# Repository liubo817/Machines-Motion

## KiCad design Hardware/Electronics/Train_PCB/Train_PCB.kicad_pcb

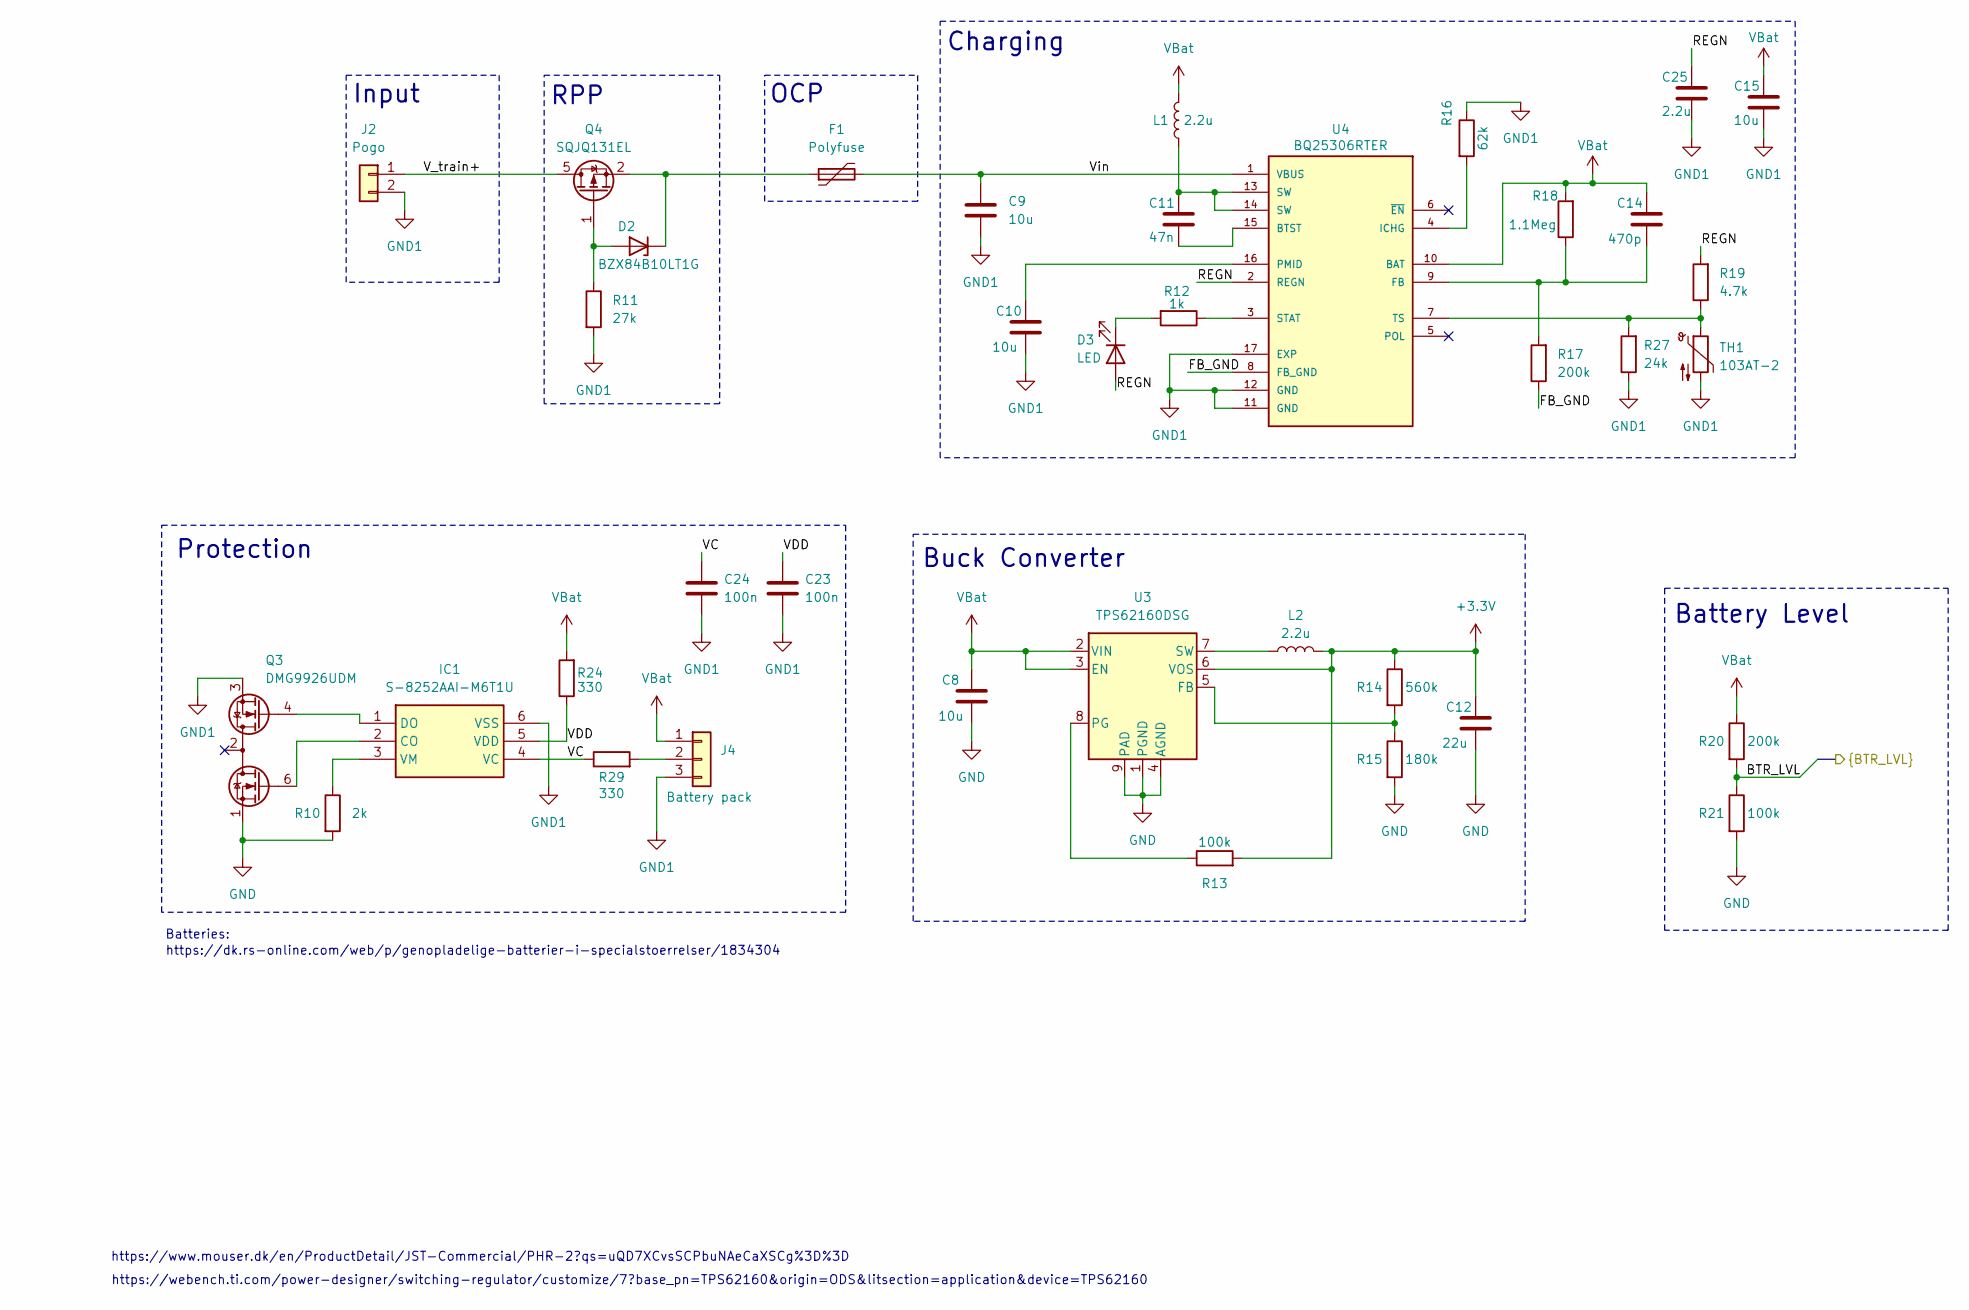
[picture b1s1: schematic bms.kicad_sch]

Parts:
C8, C9, C10, C15: 10u; C_0603_1608Metric
C11: 47n; C_0603_1608Metric
C12: 22u; C_0805_2012Metric
C14: 470p; C_0603_1608Metric
C23, C24: 100n; C_0603_1608Metric
C25: 2.2u; C_0603_1608Metric
D2: BZX84B10LT1G; SOT-23
D3: LED; 155060SS75300
F1: Polyfuse; 1812L010DR
IC1: S-8252AAI-M6T1U; SOT-23-6; Manufacturer_Part_Number S-8252ABU-M6T1U
J2: Pogo; JST_PH_S2B-PH-K_1x02_P2.00mm_Horizontal
J4: Battery pack; JST_PH_S3B-PH-K_1x03_P2.00mm_Horizontal
L1, L2: 2.2u; INDPM4042X200N
Q3: DMG9926UDM; SOT-23-6
Q4: SQJQ131EL; PowerPAK_SO-8_Single
R10: 2k; R_0603_1608Metric
R11: 27k; R_0603_1608Metric
R12: 1k; R_0603_1608Metric
R13, R21: 100k; R_0603_1608Metric
R14: 560k; R_0603_1608Metric
R15: 180k; R_0603_1608Metric
R16: 62k; R_0603_1608Metric
R17, R20: 200k; R_0603_1608Metric
R18: 1.1Meg; R_0603_1608Metric
R19: 4.7k; R_0603_1608Metric
R24, R29: 330; R_0603_1608Metric
R27: 24k; R_0603_1608Metric
TH1: 103AT-2; JST_PH_S2B-PH-K_1x02_P2.00mm_Horizontal
U3: TPS62160DSG; Texas_DSG0008A_WSON-8-1EP_2x2mm_P0.5mm_EP0.9x1.6mm_ThermalV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
U4: BQ25306RTER; WQFN-16-1EP_3x3mm_P0.5mm_EP1.68x1.68mm_ThermalVias; PARTREV A

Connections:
+3.3V: C12.1, L2.2, R13.2, R14.1, U3.6 (VOS); also elsewhere on the board
/BMS/BTR_LVL: R20.2, R21.1; also elsewhere on the board
/BMS/FB_GND: R17.1, U4.8 (FB_GND)
/BMS/REGN: C25.1, D3.2 (A), R19.2, U4.2 (REGN)
/BMS/VC: C24.1, IC1.4 (VC), R29.1
/BMS/VDD: C23.1, IC1.5 (VDD), R24.1
/BMS/V_train+: J2.1, Q4.5 (D)
/BMS/Vin: C9.1, F1.2, U4.1 (VBUS)
GND: C8.2, C12.2, Q3.1 (D1), R10.2, R15.2, R21.2, U3.1 (PGND), U3.4 (AGND), U3.9 (PAD); also elsewhere on the board
GND1: C9.2, C10.2, C15.2, C23.2, C24.2, C25.2, IC1.6 (VSS), J2.2, J4.3, Q3.3 (S2), R11.2, R16.1, R27.1, TH1.2, U4.11 (GND), U4.12 (GND), U4.17 (EXP)
unnamed: C11.1, L1.1, U4.13 (SW), U4.14 (SW)
unnamed: D2.1 (A), Q4.1 (G), R11.1
unnamed: D2.3 (K), F1.1, Q4.2 (S), Q4.3 (S), Q4.4 (S)
unnamed: D3.1 (K), R12.2
unnamed: IC1.2 (CO), Q3.6 (G1)
unnamed: IC1.1 (DO), Q3.4 (G2)
unnamed: IC1.3 (VM), R10.1
unnamed: J4.2, R29.2
unnamed: R14.2, R15.1, U3.5 (FB)
unnamed: R13.1, U3.8 (PG)
unnamed: L2.1, U3.7 (SW)
unnamed: C11.2, U4.15 (BTST)
unnamed: C14.2, R17.2, R18.1, U4.9 (FB)
unnamed: R16.2, U4.4 (ICHG)
unnamed: C10.1, U4.16 (PMID)
unnamed: R12.1, U4.3 (STAT)
unnamed: R19.1, R27.2, TH1.1, U4.7 (TS)
VBat: C8.1, C14.1, C15.1, J4.1, L1.2, R18.2, R20.1, R24.2, U3.2 (VIN), U3.3 (EN), U4.10 (BAT); also elsewhere on the board

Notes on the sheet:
https://www.mouser.dk/en/ProductDetail/JST-Commercial/PHR-2?qs=uQD7XCvsSCPbuNAeCaXSCg%3D%3D
https://dk.rs-online.com/web/p/genopladelige-batterier-i-specialstoerrelser/1834304
Batteries:
https://webench.ti.com/power-designer/switching-regulator/customize/7?base_pn=TPS62160&origin=ODS&litsection=application&device=TPS62160
Protection
Buck Converter
OCP
Input
RPP
Charging
Battery Level

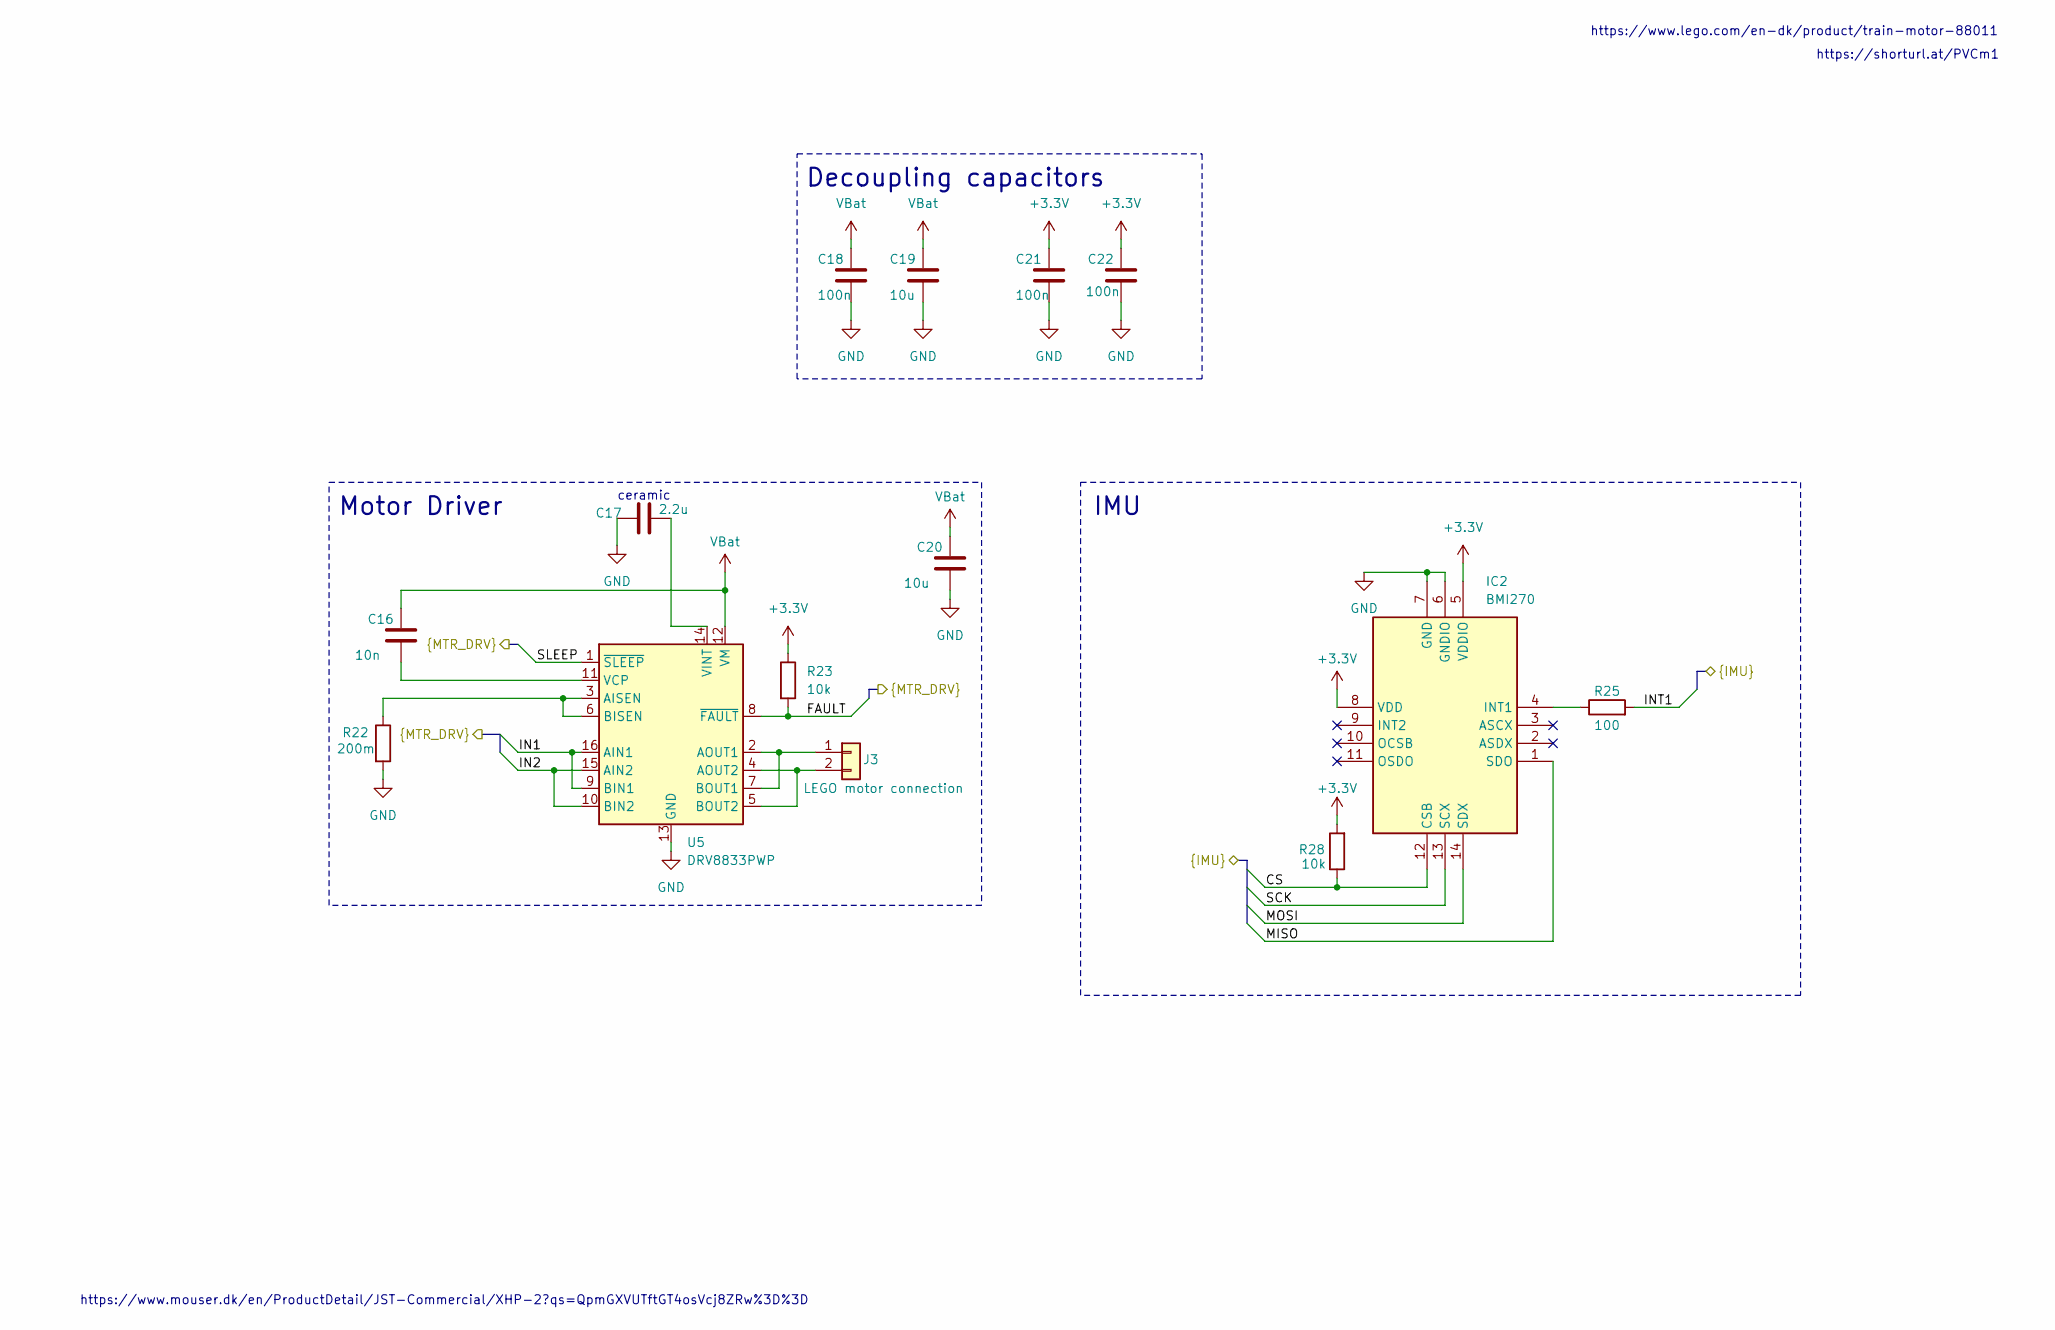
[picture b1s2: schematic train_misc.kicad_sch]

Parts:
C16: 10n; C_0603_1608Metric
C17: 2.2u; C_0603_1608Metric
C18, C21, C22: 100n; C_0603_1608Metric
C19: 10u; C_0603_1608Metric
C20: 10u; C_0805_2012Metric
IC2: BMI270; Mouser Part Number 262-BMI270
J3: LEGO motor connection; JST_XH_S2B-XH-A-1_1x02_P2.50mm_Horizontal
R22: 200m; R_0603_1608Metric
R23, R28: 10k; R_0603_1608Metric
R25: 100; R_0603_1608Metric
U5: DRV8833PWP; HTSSOP-16-1EP_4.4x5mm_P0.65mm_EP3.4x5mm_Mask2.66x2.46mm_The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

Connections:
+3.3V: C21.1, C22.1, IC2.5 (VDDIO), IC2.8 (VDD), R23.1, R28.2; also elsewhere on the board
/Esp32/CS: IC2.12 (CSB), R28.1; also elsewhere on the board
/Esp32/FAULT: R23.2, U5.8 (~FAULT); also elsewhere on the board
/Esp32/IN1: U5.9 (BIN1), U5.16 (AIN1); also elsewhere on the board
/Esp32/IN2: U5.10 (BIN2), U5.15 (AIN2); also elsewhere on the board
/Esp32/INT1: R25.2; also elsewhere on the board
/Esp32/MISO: IC2.1 (SDO); also elsewhere on the board
/Esp32/MOSI: IC2.14 (SDX); also elsewhere on the board
/Esp32/SCK: IC2.13 (SCX); also elsewhere on the board
/Esp32/SLEEP: U5.1 (~SLEEP); also elsewhere on the board
GND: C17.1, C18.2, C19.2, C20.2, C21.2, C22.2, IC2.6 (GNDIO), IC2.7 (GND), R22.2, U5.13 (GND), U5.17 (GND); also elsewhere on the board
unnamed: IC2.4 (INT1), R25.1
unnamed: J3.1, U5.2 (AOUT1), U5.7 (BOUT1)
unnamed: J3.2, U5.4 (AOUT2), U5.5 (BOUT2)
unnamed: R22.1, U5.3 (AISEN), U5.6 (BISEN)
unnamed: C16.2, U5.11 (VCP)
unnamed: C17.2, U5.14 (VINT)
VBat: C16.1, C18.1, C19.1, C20.1, U5.12 (VM); also elsewhere on the board

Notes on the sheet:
ceramic
Motor Driver
https://www.lego.com/en-dk/product/train-motor-88011
https://www.mouser.dk/en/ProductDetail/JST-Commercial/XHP-2?qs=QpmGXVUTftGT4osVcj8ZRw%3D%3D
https://shorturl.at/PVCm1
IMU
Decoupling capacitors

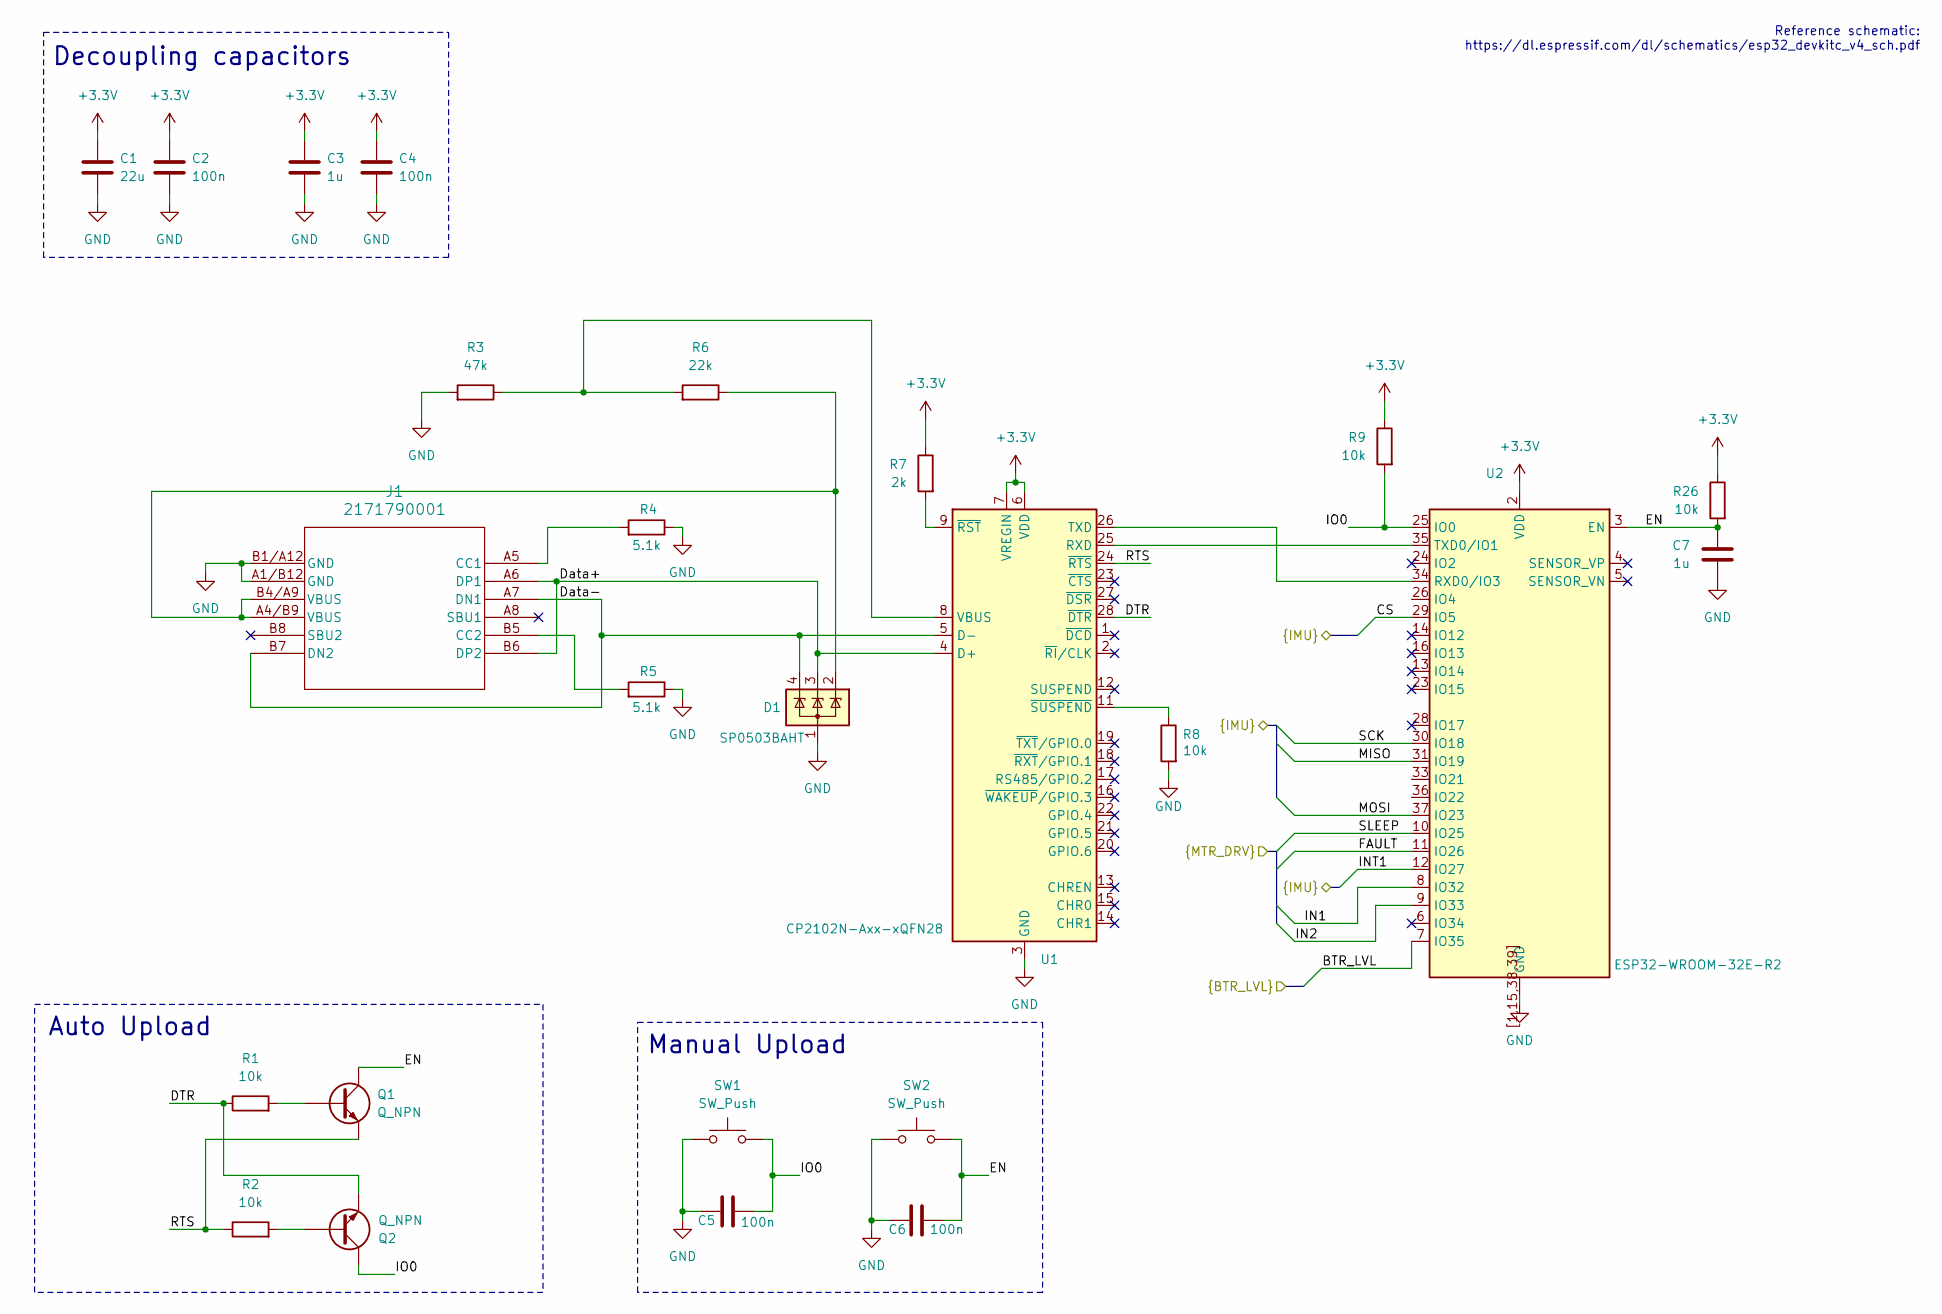
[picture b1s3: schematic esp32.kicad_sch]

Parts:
C1: 22u; C_0805_2012Metric
C2, C4, C5, C6: 100n; C_0603_1608Metric
C3, C7: 1u; C_0603_1608Metric
D1: SP0503BAHT; SP0503BAHTG
J1: 2171790001; 2171790001_MOL
Q1, Q2: Q_NPN; SOT-23-3
R1, R2, R8, R9, R26: 10k; R_0603_1608Metric
R3: 47k; R_0603_1608Metric
R4, R5: 5.1k; R_0603_1608Metric
R6: 22k; R_0603_1608Metric
R7: 2k; R_0603_1608Metric
SW1, SW2: SW_Push; EVPAWCD4A
U1: CP2102N-Axx-xQFN28; QFN-28-1EP_5x5mm_P0.5mm_EP3.1x3.1mm_ThermalVias
U2: ESP32-WROOM-32E-R2; ESP32-WROOM-32E

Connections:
+3.3V: C1.1, C2.1, C3.1, C4.1, R7.1, R9.1, R26.1, U1.6 (VDD), U1.7 (VREGIN), U2.2 (VDD); also elsewhere on the board
/BMS/BTR_LVL: U2.7 (IO35); also elsewhere on the board
/Esp32/CS: U2.29 (IO5); also elsewhere on the board
/Esp32/DTR: Q2.2 (E), R1.1, U1.28 (~DTR)
/Esp32/Data+: D1.3 (K), J1.A6 (DP1), J1.B6 (DP2), U1.4 (D+)
/Esp32/Data-: D1.4 (K), J1.A7 (DN1), J1.B7 (DN2), U1.5 (D-)
/Esp32/EN: C6.1, C7.1, Q1.3 (C), R26.2, SW2.2, U2.3 (EN)
/Esp32/FAULT: U2.11 (IO26); also elsewhere on the board
/Esp32/IN1: U2.8 (IO32); also elsewhere on the board
/Esp32/IN2: U2.9 (IO33); also elsewhere on the board
/Esp32/INT1: U2.12 (IO27); also elsewhere on the board
/Esp32/IO0: C5.1, Q2.3 (C), R9.2, SW1.2, U2.25 (IO0)
/Esp32/MISO: U2.31 (IO19); also elsewhere on the board
/Esp32/MOSI: U2.37 (IO23); also elsewhere on the board
/Esp32/RTS: Q1.2 (E), R2.1, U1.24 (~RTS)
/Esp32/SCK: U2.30 (IO18); also elsewhere on the board
/Esp32/SLEEP: U2.10 (IO25); also elsewhere on the board
GND: C1.2, C2.2, C3.2, C4.2, C5.2, C6.2, C7.2, D1.1 (A), J1.A1/B12 (GND), J1.B1/A12 (GND), R3.2, R4.1, R5.1, R8.2, SW1.1, SW2.1, U1.3 (GND), U1.29 (GND), U2.1 (GND), U2.15 (GND), U2.38 (GND), U2.39 (GND), U2.[1,15,38,39] (GND); also elsewhere on the board
unnamed: D1.2 (K), J1.A4/B9 (VBUS), J1.B4/A9 (VBUS), R6.1
unnamed: J1.A5 (CC1), R4.2
unnamed: J1.B5 (CC2), R5.2
unnamed: Q1.1 (B), R1.2
unnamed: Q2.1 (B), R2.2
unnamed: U1.25 (RXD), U2.35 (TXD0/IO1)
unnamed: U1.26 (TXD), U2.34 (RXD0/IO3)
unnamed: R3.1, R6.2, U1.8 (VBUS)
unnamed: R7.2, U1.9 (~RST)
unnamed: R8.1, U1.11 (~SUSPEND)

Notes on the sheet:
Reference schematic: https://dl.espressif.com/dl/schematics/esp32_devkitc_v4_sch.pdf
Decoupling capacitors
Manual Upload
Auto Upload

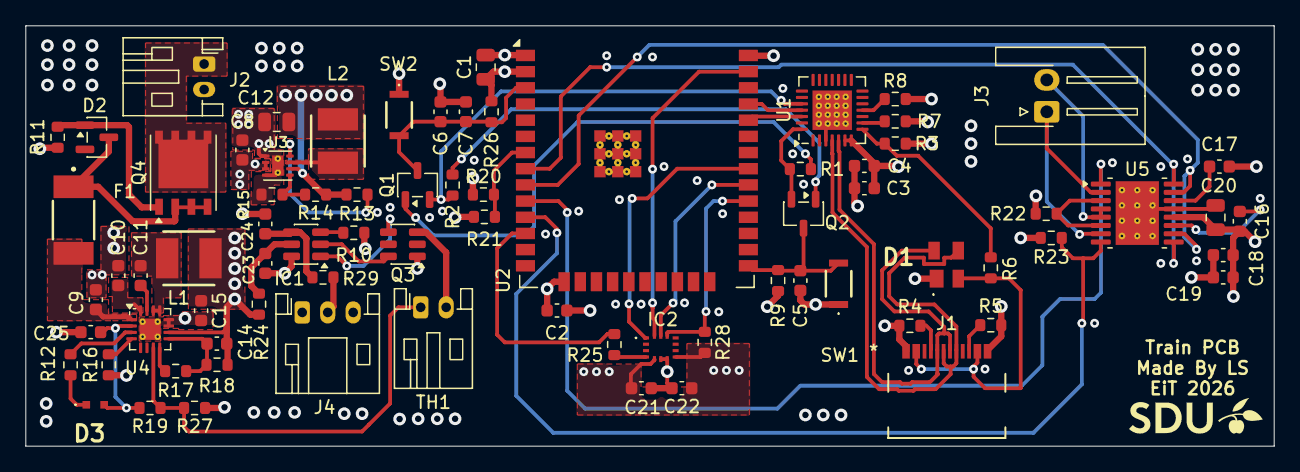
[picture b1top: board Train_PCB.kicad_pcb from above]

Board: 4 copper layers, 98.0 x 33.0 mm, 77 parts (0 on the bottom side), 59 nets.

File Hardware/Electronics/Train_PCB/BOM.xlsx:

Qty | Value | Parts | Device | Package | Description | Mouser | RS | Digikey
2 | 22uF | C1, C12 | C | C0805 | Capacitor
7 | 100nF | C2, C4, C5, C6, C18, C21, C22 | C | C0603 | Capacitor
2 | 1uF | C3,C7 | C | C0603 | Capacitor
5 | 10uF | C8, C9, C10, C15, C19 | C | C0603 | Capacitor
1 | 47nF | C11 | C | C0603 | Capacitor
2 | 2.2uF | C13, C17 | C | C0603 | Capacitor
1 | 470pF | C14 | C | C0603 | Capacitor
1 | 10nF | C16 | C | C0603 | Capacitor
1 | 10uF | C20 | C | C0805 | Capacitor
1 | SP0503BAHT | D1 | SP0503BAHT | SOT-143-4 | Diode | 576-SP0503BAHTG
1 | BZX84B10LT1G | D2 | BZX84B10LT1G | SOT-23 | Diode |  | 484-3306
1 | LED | D3 | LED | SMD, 0603 (1608 metric) | LED | 710-155060SS75300
1 | Polyfuse | F1 | 1812L150/24MR | SMD, 1812 (4532 metric) | Polyfuse | 576-1812L150/24MR
1 | BMI270 | IC2 | BMI270 | SMD, LGA-14 | IMU | 262-BMI270
1 | USB type C | J1 | USB type C | SMD | Molex USB type C connector | 538-217179-0001
2 | JST S2B-PH-K-S-GW | J2, TH1 | JST S2B-PH-K-S-GW | THT | JST 2 pin angled connector - 2mm | 306-S2BPHKSGWPP
1 | JST S2B-XH-A-1(LF)(SN) | J3 | JST S2B-XH-A-1(LF)(SN) | THT | JST 2 pin angled connector - 2.5mm | 306-S2BXHA1LFSN
1 | JST S3B-PH-K-S (LF)(SN) | J4 | JST S3B-PH-K-S (LF)(SN) | THT | JST 3 pin angled connector - 2mm |  | 820-1504
2 | 2.2uH | L1, L2 | L | SMD | Inductor | 673-PA4332222NLT
2 | Q_NPN | Q1, Q2 | SS8050-G | SOT-23-3 | BJT | 750-SS8050-G
1 | DMG9926UDM | Q3 | DMG9926UDM | SOT-26-6 | DUAL N-CHANNEL MOSFET | 621-DMG9926UDM-7
1 | SQJQ131EL | Q4 | SQJQ131EL | PowerPAK SO-8L | P-Channel MOSFET | 78-SQJ141ELP-T1_GE3
7 | 10k | R1, R2, R8, R9, R23, R26, R28 | R | R0603 | Resistor
1 | 47k | R3 | R | R0603 | Resistor
2 | 5.1k | R4, R5 | R | R0603 | Resistor
1 | 22k | R6 | R | R0603 | Resistor
1 | 2k | R7 | R | R0603 | Resistor
1 | 2.7k | R10 | R | R0603 | Resistor
1 | 27k | R11 | R | R0603 | Resistor
1 | 1k | R12 | R | R0603 | Resistor
2 | 100k | R13, R21 | R | R0603 | Resistor
1 | 560k | R14 | R | R0603 | Resistor
1 | 180k | R15 | R | R0603 | Resistor
1 | 62k | R16 | R | R0603 | Resistor
2 | 200k | R17, R20 | R | R0603 | Resistor
1 | 1.1Meg | R18 | R | R0603 | Resistor
1 | 4.7k | R19 | R | R0603 | Resistor
1 | 200m | R22 | R | R0603 | Current Sense Resistor | 71-RCWE0603R200FKEA
1 | 100 | R25 | R | R0603 | Resistor
1 | 24k | R27 | R | R0603 | Resistor
2 | EVP-AWCD4A | SW1, SW2 | EVP-AWCD4A | SMD | Light Touch Switch |  |  | P123439TR-ND
1 | CP2102N-Axx-xQFN28 | U1 | CP2102N-Axx-xQFN28 | QFN28 | Single-Chip USB-to-UART Data Transfer |  | 187-1341
1 | ESP32-WROOM-32E-N16 | U2 | ESP32-WROOM-32E-N16 | SMD | ESP32-WROOM | 356-ESP32WRM32E128PH
1 | TPS62160DSG | U3 | TPS62160DSG | SMD, WSON-8 | Switching Voltage Regulator | 595-TPS62160DSGR
1 | BQ25306RTER | U4 | BQ25306RTER | SMD, WQFN-16 | Battery Charger | 595-BQ25306RTER
1 | DRV8833PWP | U5 | DRV8833PWP | SMD, HTSSOP-16 | Motor Driver | 595-DRV8833PWPR
1 | HY2122 EB1A | IC1 | HY2122 EB1A | SOT-23-6 | Battery Management IC | https://www.lcsc.com/product-detail/C458515.html
